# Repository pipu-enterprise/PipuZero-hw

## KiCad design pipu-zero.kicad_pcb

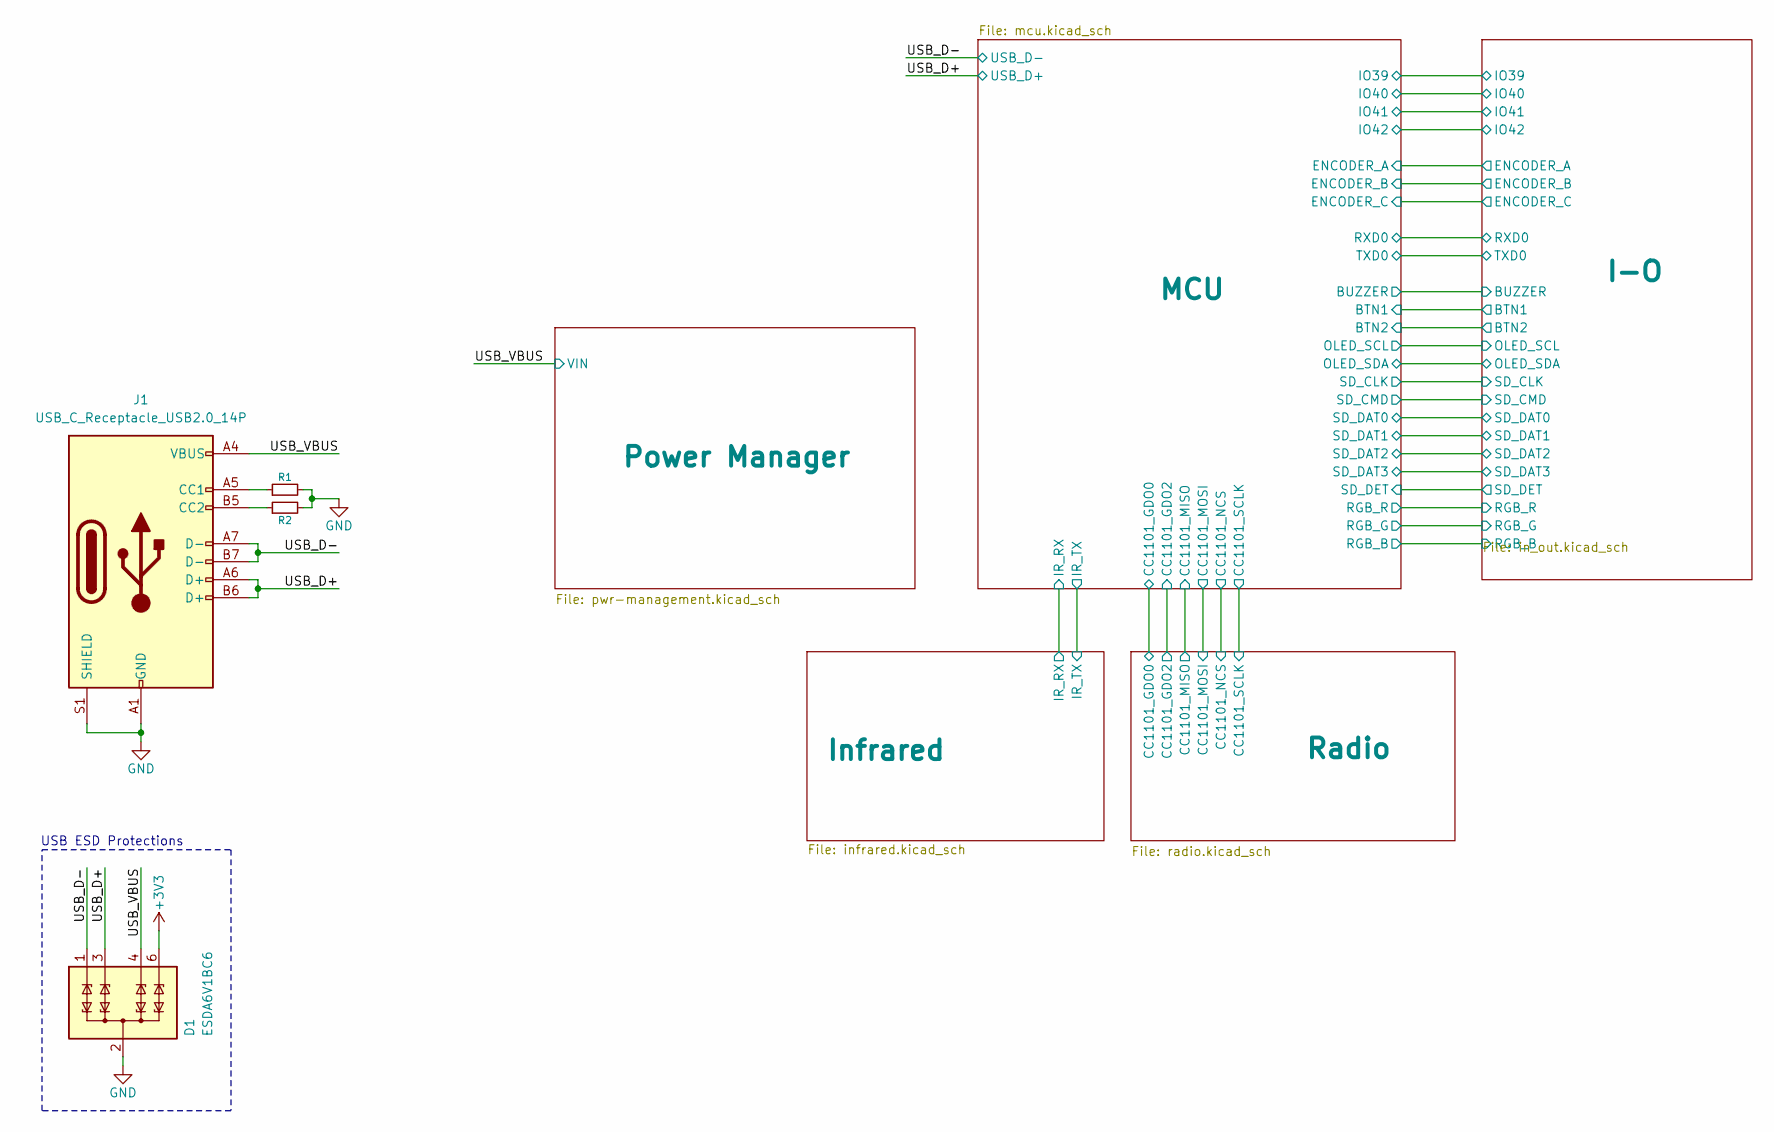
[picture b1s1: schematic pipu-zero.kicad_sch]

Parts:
D1: ESDA6V1BC6; SOT-23-6
J1: USB_C_Receptacle_USB2.0_14P; HRO_TYPE-C-31-M-12
R1, R2: 5.1k; R_0603_1608Metric

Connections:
+3V3: D1.6 (TVS4); also elsewhere on the board
/USB_D+: D1.3 (TVS2), J1.A6 (D+), J1.B6 (D+); also elsewhere on the board
/USB_D-: D1.1 (TVS1), J1.A7 (D-), J1.B7 (D-); also elsewhere on the board
/USB_VBUS: D1.4 (TVS3), J1.A4 (VBUS), J1.A9 (VBUS), J1.B4 (VBUS), J1.B9 (VBUS); also elsewhere on the board
GND: D1.2 (COM), D1.5 (COM), J1.A1 (GND), J1.A12 (GND), J1.B1 (GND), J1.B12 (GND), J1.S1 (SHIELD), R1.2, R2.2; also elsewhere on the board
unnamed: J1.A5 (CC1), R1.1
unnamed: J1.B5 (CC2), R2.1

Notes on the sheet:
USB ESD Protections

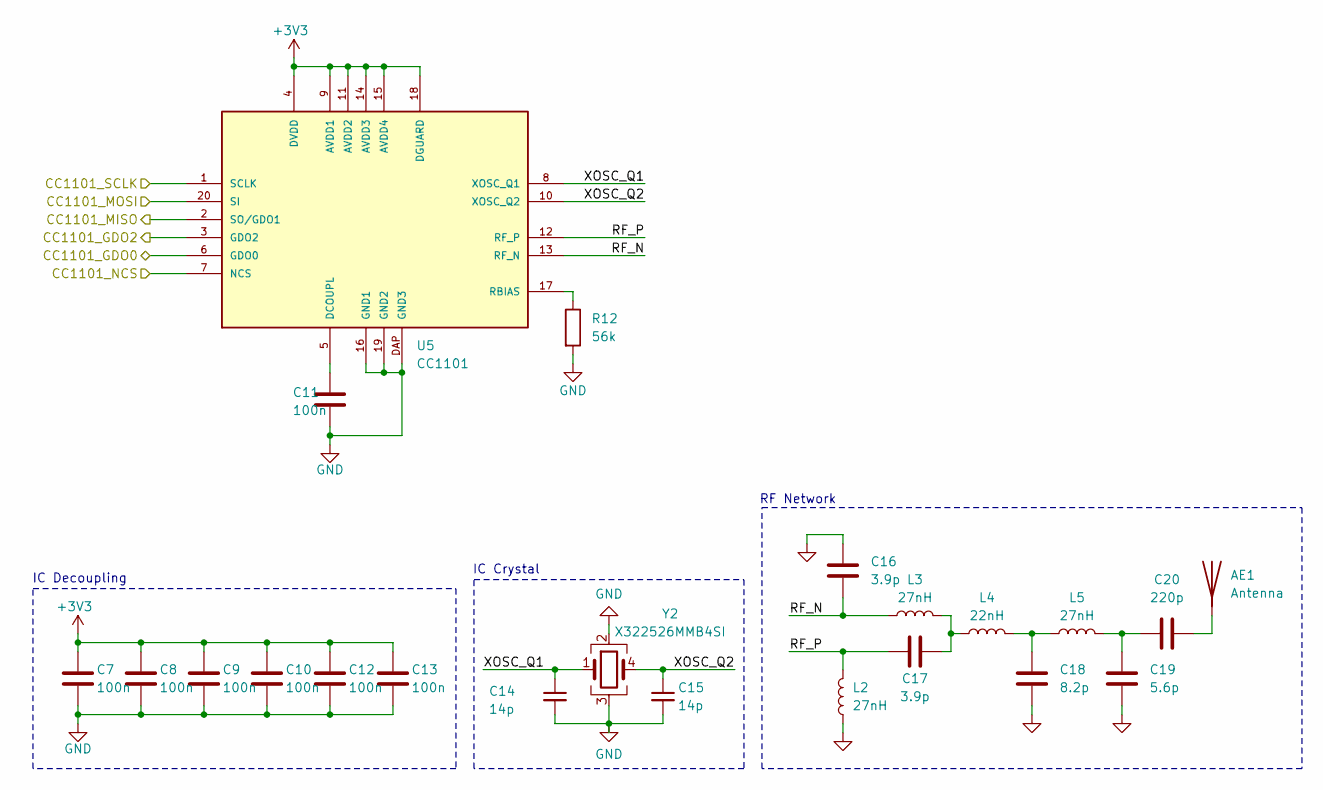
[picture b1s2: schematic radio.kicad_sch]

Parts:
AE1: Antenna; PinHeader_1x01_P2.54mm_Vertical
C7, C8, C9, C10, C12, C13: 100n; C_0402_1005Metric
C11: 100n; C_0603_1608Metric
C14, C15: 14p; C_0402_1005Metric
C16, C17: 3.9p; C_0603_1608Metric
C18: 8.2p; C_0603_1608Metric
C19: 5.6p; C_0603_1608Metric
C20: 220p; C_0603_1608Metric
L2, L3, L5: 27nH; L_0603_1608Metric
L4: 22nH; L_0603_1608Metric
R12: 56k; R_0603_1608Metric
U5: CC1101; QLP20
Y2: X322526MMB4SI; Crystal_SMD_3225-4Pin_3.2x2.5mm_HandSoldering

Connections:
+3V3: C7.1, C8.1, C9.1, C10.1, C12.1, C13.1, U5.4 (DVDD), U5.9 (AVDD1), U5.11 (AVDD2), U5.14 (AVDD3), U5.15 (AVDD4), U5.18 (DGUARD); also elsewhere on the board
/MCU/CC1101_GDO0: U5.6 (GDO0); also elsewhere on the board
/MCU/CC1101_GDO2: U5.3 (GDO2); also elsewhere on the board
/MCU/CC1101_MISO: U5.2 (SO/GDO1); also elsewhere on the board
/MCU/CC1101_MOSI: U5.20 (SI); also elsewhere on the board
/MCU/CC1101_NCS: U5.7 (NCS); also elsewhere on the board
/MCU/CC1101_SCLK: U5.1 (SCLK); also elsewhere on the board
/Radio/RF_N: C16.2, L3.1, U5.13 (RF_N)
/Radio/RF_P: C17.1, L2.2, U5.12 (RF_P)
/Radio/XOSC_Q1: C14.1, U5.8 (XOSC_Q1), Y2.1
/Radio/XOSC_Q2: C15.1, U5.10 (XOSC_Q2), Y2.4
GND: C7.2, C8.2, C9.2, C10.2, C11.2, C12.2, C13.2, C14.2, C15.2, C16.1, C18.2, C19.2, L2.1, R12.2, U5.16 (GND1), U5.19 (GND2), U5.DAP (GND3), Y2.2, Y2.3; also elsewhere on the board
unnamed: AE1.1, C20.2
unnamed: C17.2, L3.2, L4.1
unnamed: C18.1, L4.2, L5.1
unnamed: C19.1, C20.1, L5.2
unnamed: C11.1, U5.5 (DCOUPL)
unnamed: R12.1, U5.17 (RBIAS)

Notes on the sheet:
IC Decoupling
RF Network
IC Crystal

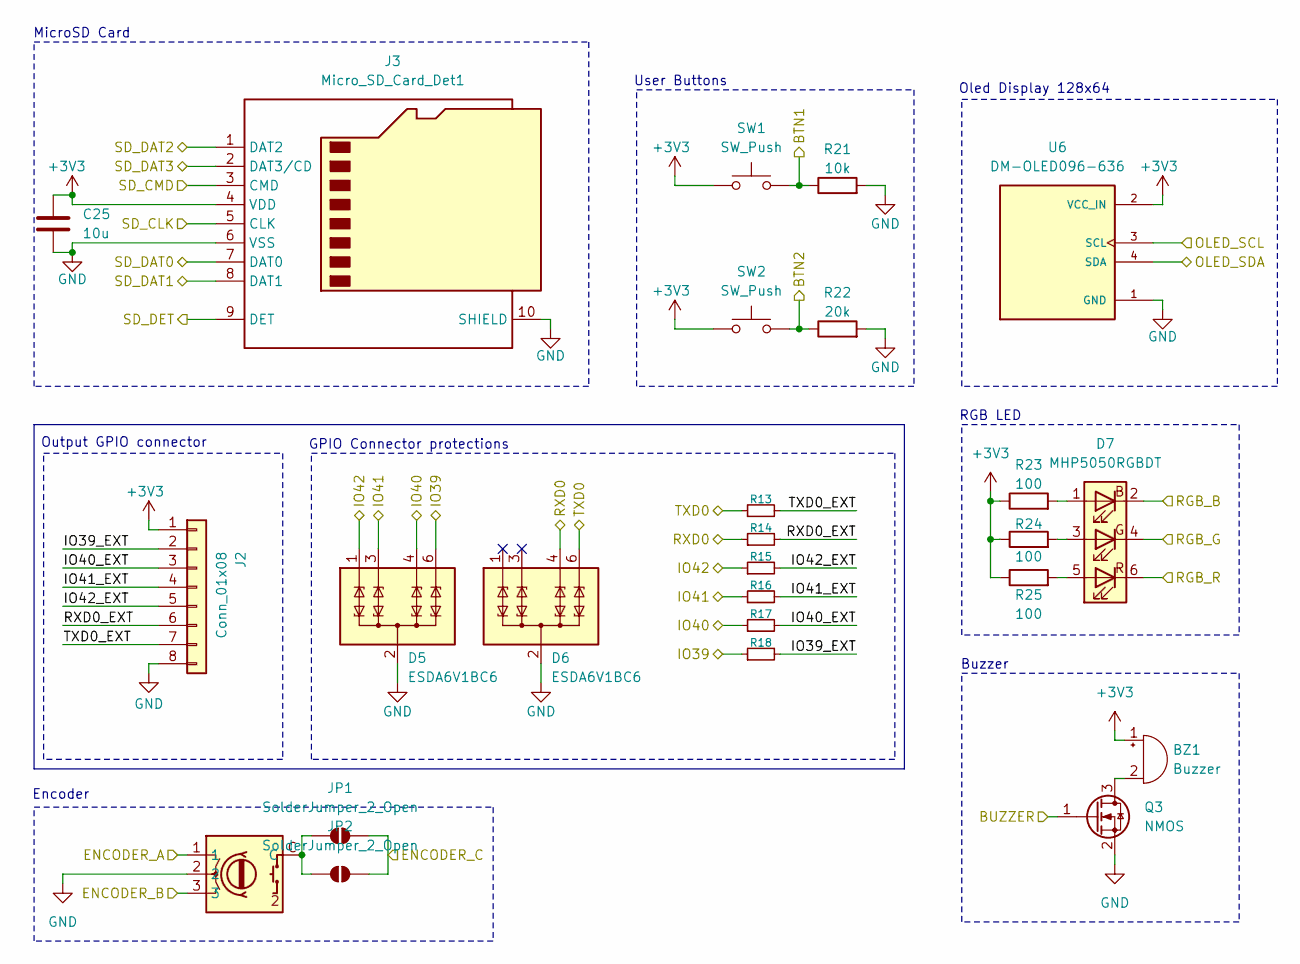
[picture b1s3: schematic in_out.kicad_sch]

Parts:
BZ1: Buzzer; Buzzer_CUI_CPT-9019S-SMT
C25: 10u; C_0805_2012Metric
D5, D6: ESDA6V1BC6; SOT-23-6
D7: MHP5050RGBDT; LED_RGB_5050-6
J2: Conn_01x08; PinSocket_1x08_P2.54mm_Horizontal
J3: Micro_SD_Card_Det1; TF-SMD_A-MICROTF-1.85A
JP1, JP2: SolderJumper_2_Open; SolderJumper-2_P1.3mm_Open_TrianglePad1.0x1.5mm
Q3: NMOS; SOT-23
R13, R23, R24, R25: 100; R_0603_1608Metric
R14, R15, R16, R17, R18: 100R; R_0603_1608Metric
R21: 10k; R_0603_1608Metric
R22: 20k; R_0603_1608Metric
SW1, SW2: SW_Push; SW_SPST_SKQG_WithoutStem
U6: DM-OLED096-636; MODULE_DM-OLED096-636; PARTREV 2018-09-10
U8: encoder

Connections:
+3V3: BZ1.1 (+), C25.1, J2.1, J3.4 (VDD), R23.1, R24.1, R25.1, SW1.1, SW2.1, U6.2 (VCC_IN); also elsewhere on the board
/I-O/BTN1: R21.1, SW1.2; also elsewhere on the board
/I-O/BTN2: R22.1, SW2.2; also elsewhere on the board
/I-O/BUZZER: Q3.1 (G); also elsewhere on the board
/I-O/ENCODER_A: U8.1; also elsewhere on the board
/I-O/ENCODER_B: U8.3; also elsewhere on the board
/I-O/ENCODER_C: JP1.2 (B), JP2.2 (B); also elsewhere on the board
/I-O/IO39: D5.6 (TVS4), R18.1; also elsewhere on the board
/I-O/IO39_EXT: J2.2, R18.2
/I-O/IO40: D5.4 (TVS3), R17.1; also elsewhere on the board
/I-O/IO40_EXT: J2.3, R17.2
/I-O/IO41: D5.3 (TVS2), R16.1; also elsewhere on the board
/I-O/IO41_EXT: J2.4, R16.2
/I-O/IO42: D5.1 (TVS1), R15.1; also elsewhere on the board
/I-O/IO42_EXT: J2.5, R15.2
/I-O/OLED_SCL: U6.3 (SCL); also elsewhere on the board
/I-O/OLED_SDA: U6.4 (SDA); also elsewhere on the board
/I-O/RGB_B: D7.2 (BK); also elsewhere on the board
/I-O/RGB_G: D7.4 (GK); also elsewhere on the board
/I-O/RGB_R: D7.6 (RK); also elsewhere on the board
/I-O/RXD0: D6.4 (TVS3), R14.1; also elsewhere on the board
/I-O/RXD0_EXT: J2.6, R14.2
/I-O/SD_CLK: J3.5 (CLK); also elsewhere on the board
/I-O/SD_CMD: J3.3 (CMD); also elsewhere on the board
/I-O/SD_DAT0: J3.7 (DAT0); also elsewhere on the board
/I-O/SD_DAT1: J3.8 (DAT1); also elsewhere on the board
/I-O/SD_DAT2: J3.1 (DAT2); also elsewhere on the board
/I-O/SD_DAT3: J3.2 (DAT3/CD); also elsewhere on the board
/I-O/SD_DET: J3.9 (DET); also elsewhere on the board
/I-O/TXD0: D6.6 (TVS4), R13.1; also elsewhere on the board
/I-O/TXD0_EXT: J2.7, R13.2
GND: C25.2, D5.2 (COM), D5.5 (COM), D6.2 (COM), D6.5 (COM), J2.8, J3.6 (VSS), J3.10 (SHIELD), Q3.2 (S), R21.2, R22.2, U6.1 (GND), U8.2; also elsewhere on the board
unnamed: BZ1.2 (-), Q3.3 (D)
unnamed: D7.1 (BA), R23.2
unnamed: D7.3 (GA), R24.2
unnamed: D7.5 (RA), R25.2
unnamed: JP1.1 (A), JP2.1 (A), U8.C

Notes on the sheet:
MicroSD Card
GPIO Connector protections
Output GPIO connector
Encoder
Oled Display 128x64
User Buttons
RGB LED
Buzzer

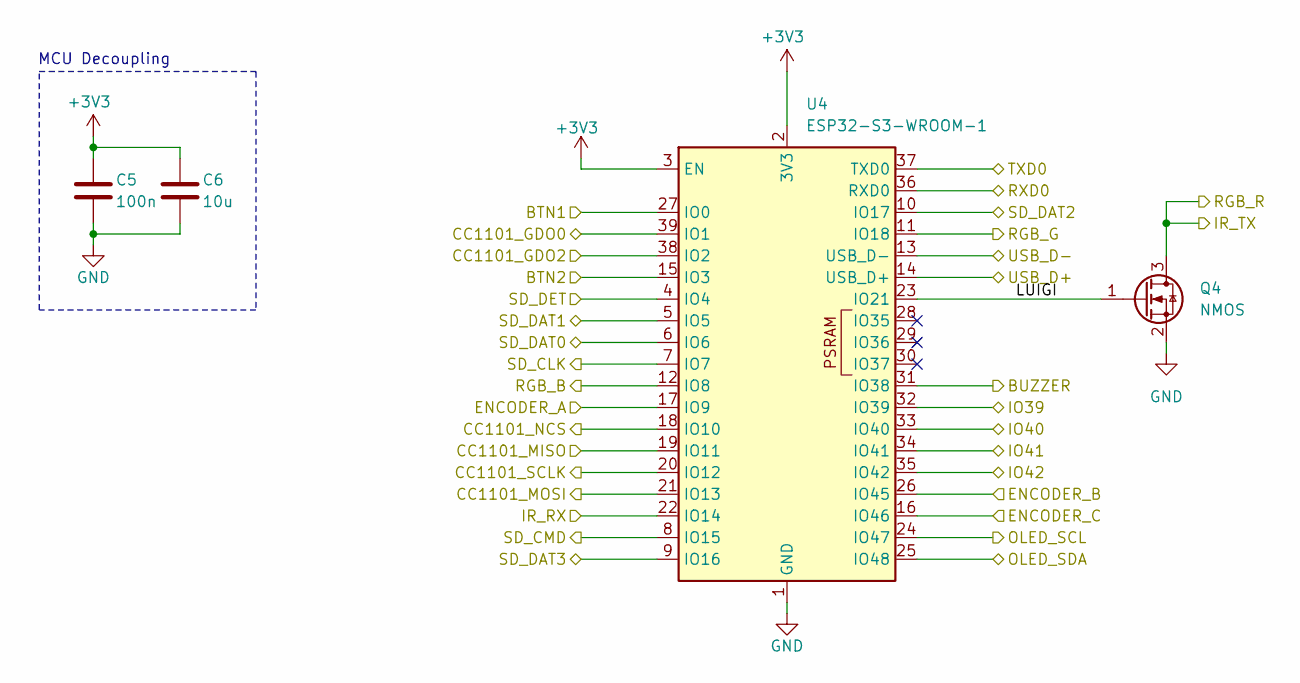
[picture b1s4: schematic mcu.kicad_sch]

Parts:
C5: 100n; C_0603_1608Metric
C6: 10u; C_0603_1608Metric
Q4: NMOS; SOT-23
U4: ESP32-S3-WROOM-1

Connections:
+3V3: C5.1, C6.1, U4.2 (3V3), U4.3 (EN); also elsewhere on the board
/I-O/BTN1: U4.27 (IO0); also elsewhere on the board
/I-O/BTN2: U4.15 (IO3); also elsewhere on the board
/I-O/BUZZER: U4.31 (IO38); also elsewhere on the board
/I-O/ENCODER_A: U4.17 (IO9); also elsewhere on the board
/I-O/ENCODER_B: U4.26 (IO45); also elsewhere on the board
/I-O/ENCODER_C: U4.16 (IO46); also elsewhere on the board
/I-O/IO39: U4.32 (IO39); also elsewhere on the board
/I-O/IO40: U4.33 (IO40); also elsewhere on the board
/I-O/IO41: U4.34 (IO41); also elsewhere on the board
/I-O/IO42: U4.35 (IO42); also elsewhere on the board
/I-O/OLED_SCL: U4.24 (IO47); also elsewhere on the board
/I-O/OLED_SDA: U4.25 (IO48); also elsewhere on the board
/I-O/RGB_B: U4.12 (IO8); also elsewhere on the board
/I-O/RGB_G: U4.11 (IO18); also elsewhere on the board
/I-O/RGB_R: Q4.3 (D); also elsewhere on the board
/I-O/RXD0: U4.36 (RXD0); also elsewhere on the board
/I-O/SD_CLK: U4.7 (IO7); also elsewhere on the board
/I-O/SD_CMD: U4.8 (IO15); also elsewhere on the board
/I-O/SD_DAT0: U4.6 (IO6); also elsewhere on the board
/I-O/SD_DAT1: U4.5 (IO5); also elsewhere on the board
/I-O/SD_DAT2: U4.10 (IO17); also elsewhere on the board
/I-O/SD_DAT3: U4.9 (IO16); also elsewhere on the board
/I-O/SD_DET: U4.4 (IO4); also elsewhere on the board
/I-O/TXD0: U4.37 (TXD0); also elsewhere on the board
/Infrared/IR_RX: U4.22 (IO14); also elsewhere on the board
/MCU/CC1101_GDO0: U4.39 (IO1); also elsewhere on the board
/MCU/CC1101_GDO2: U4.38 (IO2); also elsewhere on the board
/MCU/CC1101_MISO: U4.19 (IO11); also elsewhere on the board
/MCU/CC1101_MOSI: U4.21 (IO13); also elsewhere on the board
/MCU/CC1101_NCS: U4.18 (IO10); also elsewhere on the board
/MCU/CC1101_SCLK: U4.20 (IO12); also elsewhere on the board
/MCU/LUIGI: Q4.1 (G), U4.23 (IO21)
/USB_D+: U4.14 (USB_D+); also elsewhere on the board
/USB_D-: U4.13 (USB_D-); also elsewhere on the board
GND: C5.2, C6.2, Q4.2 (S), U4.1 (GND), U4.40 (GND), U4.41 (GND); also elsewhere on the board

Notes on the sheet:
MCU Decoupling

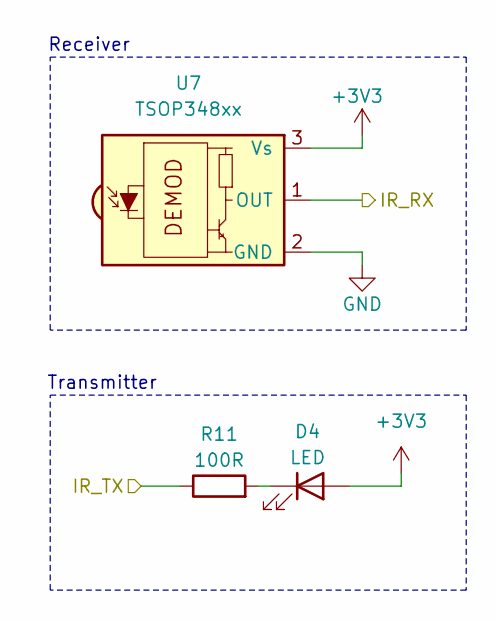
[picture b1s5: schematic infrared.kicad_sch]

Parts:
D4: LED; LED_D3.0mm_Horizontal_O1.27mm_Z2.0mm
R11: 100R; R_0603_1608Metric
U7: TSOP348xx; Vishay_MOLD-3Pin

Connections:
+3V3: D4.2 (A), U7.3 (Vs); also elsewhere on the board
/I-O/RGB_R: R11.1; also elsewhere on the board
/Infrared/IR_RX: U7.1 (OUT); also elsewhere on the board
GND: U7.2 (GND); also elsewhere on the board
unnamed: D4.1 (K), R11.2

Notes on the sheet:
Transmitter
Receiver

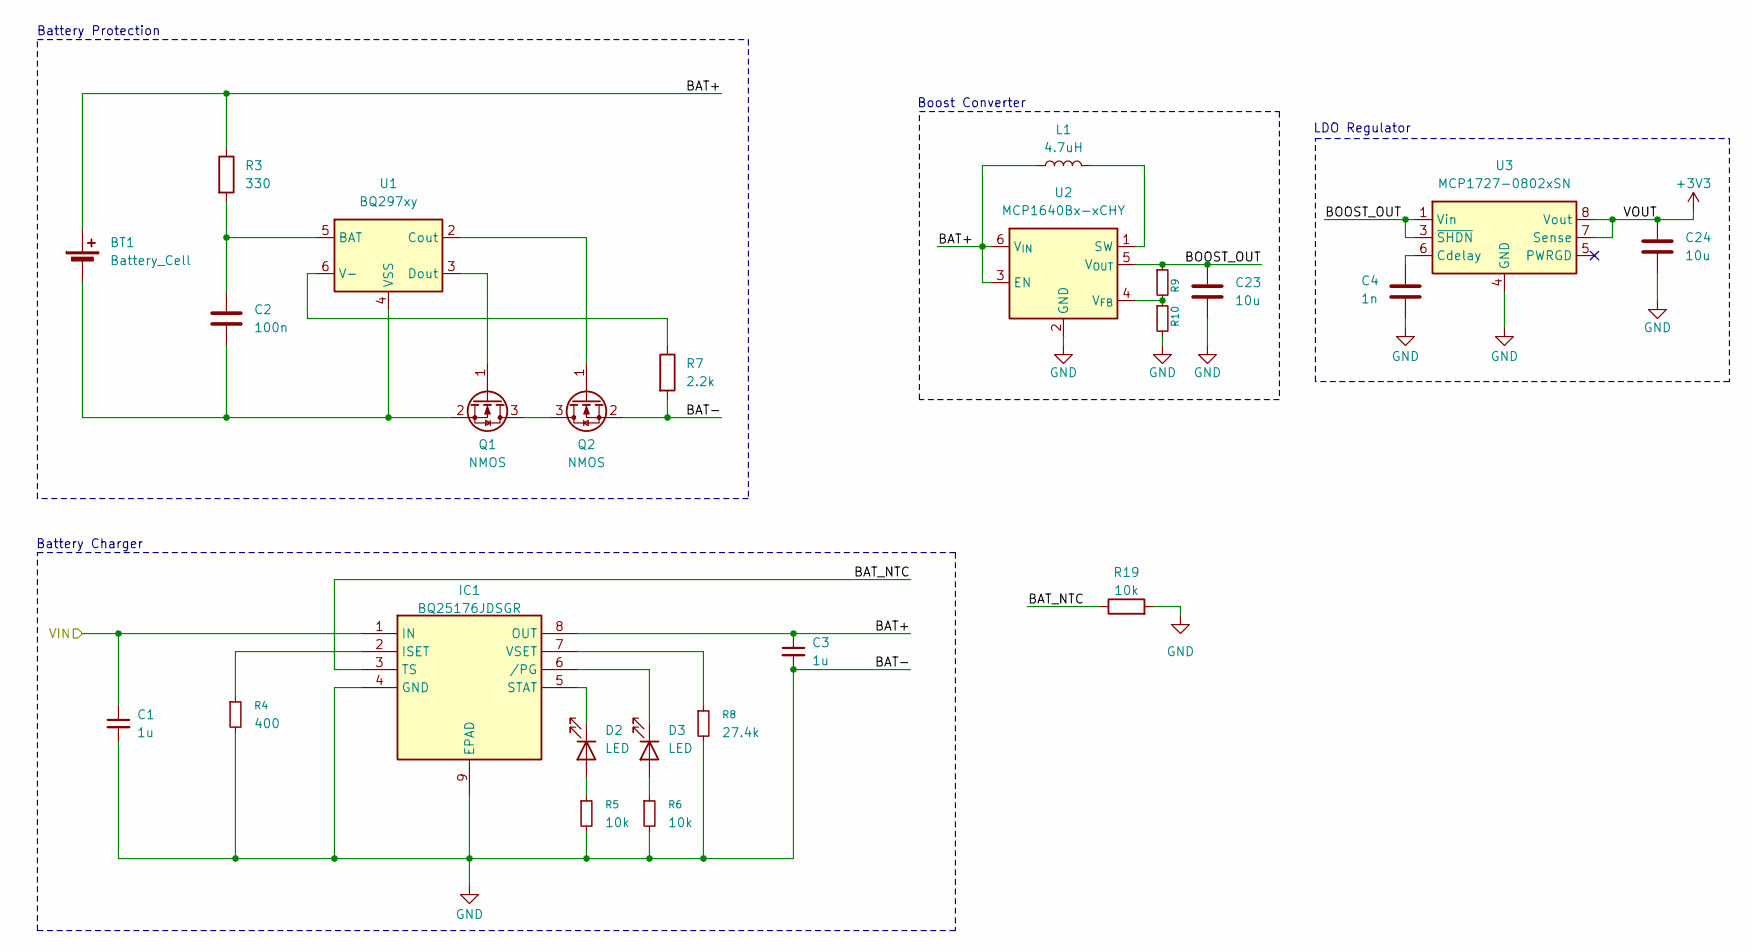
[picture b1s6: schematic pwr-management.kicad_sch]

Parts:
BT1: Battery_Cell; PinSocket_1x02_P2.54mm_Vertical
C1, C3: 1u; C_0603_1608Metric
C2: 100n; C_0603_1608Metric
C4: 1n; C_0603_1608Metric
C23, C24: 10u; C_0805_2012Metric
D2, D3: LED; LED_0805_2012Metric
IC1: BQ25176JDSGR; SON50P200X200X80-9N; Mouser Part Number 595-BQ25176JDSGR
L1: 4.7uH; CPT9019SSMTTR
Q1, Q2: NMOS; SOT-23
R3: 330; R_0603_1608Metric
R4: 400; R_0603_1608Metric
R5, R6, R19: 10k; R_0603_1608Metric
R7: 2.2k; R_0603_1608Metric
R8: 27.4k; R_0603_1608Metric
R9: 976; R_0603_1608Metric
R10: 562; R_0603_1608Metric
U1: BQ297xy; WSON-6_1.5x1.5mm_P0.5mm
U2: MCP1640Bx-xCHY; SOT-23-6
U3: MCP1727-0802xSN; SOIC-8_3.9x4.9mm_P1.27mm

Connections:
+3V3: C24.1, U3.7 (Sense), U3.8 (Vout); also elsewhere on the board
/Power Manager/BAT+: BT1.1 (+), C3.1, IC1.8 (OUT), L1.1, R3.1, U2.3 (EN), U2.6 (V_{IN})
/Power Manager/BAT_NTC: IC1.3 (TS), R19.1
/Power Manager/BOOST_OUT: C23.1, R9.1, U2.5 (V_{OUT}), U3.1 (Vin), U3.2 (Vin), U3.3 (~SHDN)
/USB_VBUS: C1.1, IC1.1 (IN); also elsewhere on the board
GND: C1.2, C3.2, C4.2, C23.2, C24.2, IC1.4 (GND), IC1.9 (EPAD), Q2.2 (S), R4.2, R5.2, R6.2, R7.2, R8.2, R10.2, R19.2, U2.2 (GND), U3.4 (GND); also elsewhere on the board
unnamed: BT1.2 (-), C2.2, Q1.2 (S), U1.4 (VSS)
unnamed: D2.2 (A), R5.1
unnamed: D2.1 (K), IC1.5 (STAT)
unnamed: D3.2 (A), R6.1
unnamed: D3.1 (K), IC1.6 (/PG)
unnamed: IC1.2 (ISET), R4.1
unnamed: IC1.7 (VSET), R8.1
unnamed: Q1.3 (D), Q2.3 (D)
unnamed: Q1.1 (G), U1.3 (Dout)
unnamed: Q2.1 (G), U1.2 (Cout)
unnamed: C2.1, R3.2, U1.5 (BAT)
unnamed: R7.1, U1.6 (V-)
unnamed: L1.2, U2.1 (SW)
unnamed: R9.2, R10.1, U2.4 (V_{FB})
unnamed: C4.1, U3.6 (Cdelay)

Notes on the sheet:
Battery Protection
Boost Converter
Battery Charger
LDO Regulator

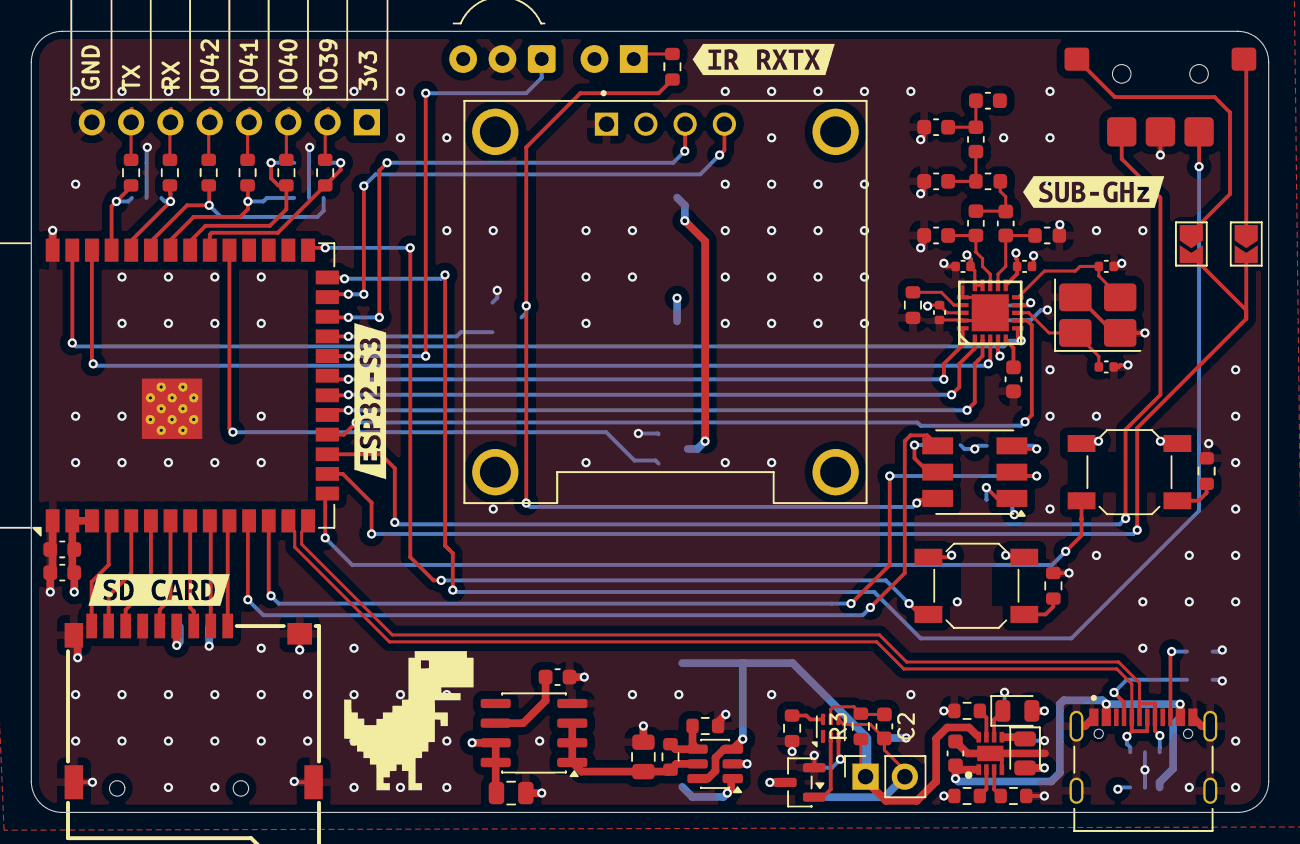
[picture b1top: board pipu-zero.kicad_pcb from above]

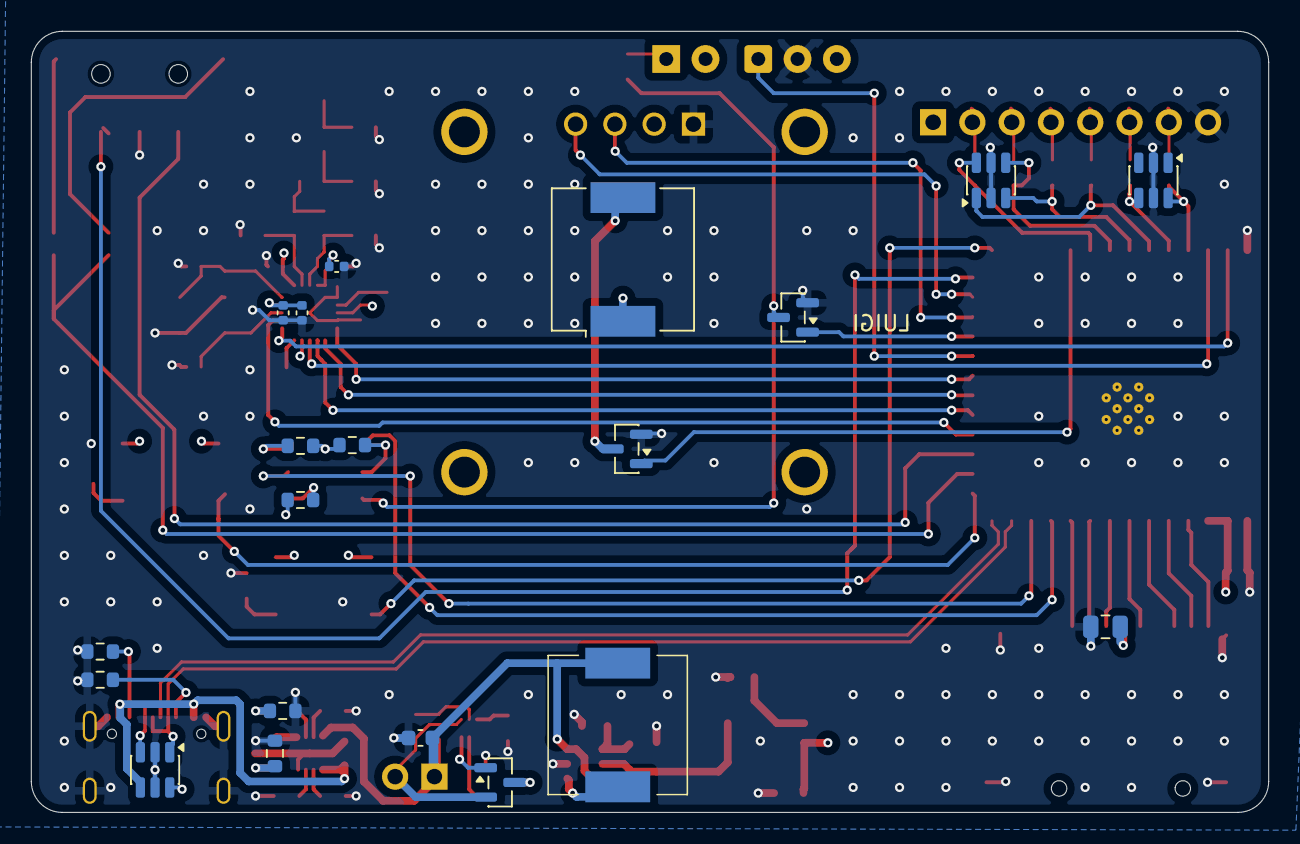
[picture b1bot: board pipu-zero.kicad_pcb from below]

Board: 4 copper layers, 80.0 x 50.5 mm, 86 parts (20 on the bottom side), 78 nets.

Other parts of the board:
kibuzzard-6926C4AC: G***; kibuzzard-6926C4AC
kibuzzard-6926C4FB: G***; kibuzzard-6926C4FB
kibuzzard-6926C46D: G***; kibuzzard-6926C46D
kibuzzard-6926C534: G***; kibuzzard-6926C534

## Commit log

2025-10-25 add kicad project
2025-10-25 add cc1101 library
2025-10-25 add BQ25176 library
2025-10-25 add BQ2970 library
2025-10-25 add libraries to kicad
2025-10-25 initial schematic
2025-10-25 add TSOP75338TR library
2025-10-25 component placement inside schematic
2025-10-26 add esd usb protections
2025-10-26 add RGB led
2025-10-26 add gitignore
2025-10-26 .gitignore is now working
2025-10-26 fix rgb led labels
2025-10-26 add external gpio connector
2025-10-26 fix BQ25176J library
2025-10-26 add usbc esd protections
2025-10-26 Add battery handling
2025-10-26 add missing connections inside MCU
2025-10-26 add boost converter and ldo regulator
2025-10-26 set initial component footprints
2025-10-27 Add footprints
2025-10-27 Add buzzer library
2025-10-27 Add inductor library
2025-10-27 Initial pcb component placement
2025-10-28 add backups folder to .gitignore
2025-10-28 retroactively apply .gitignore
2025-10-28 modify ios
2025-10-28 Add encoder footprint
2025-10-28 Add encoder symbol
2025-10-28 update pcb and schematic
2025-10-28 Add encoder to schematic
2025-10-28 Fix encoder schematic
2025-10-28 Add bypass capacitors
2025-10-28 Fix usbc footprint
2025-10-28 finish component placement on pcb
2025-10-28 add layer filling
2025-10-29 initial component routing
2025-10-29 component routing
2025-10-29 add resistor footprint
2025-11-04 routing
2025-11-04 add power supply gaza strip
2025-11-04 giovanni
2025-11-04 change output connector pinout
2025-11-04 finish routing
2025-11-04 add antenna connector
2025-11-17 add cc1101 passives
2025-11-19 LUIGI
2025-11-26 add silkscreen
2025-11-26 Add top and bottom ground plane
2025-11-26 fix drc
2025-11-26 add vias
